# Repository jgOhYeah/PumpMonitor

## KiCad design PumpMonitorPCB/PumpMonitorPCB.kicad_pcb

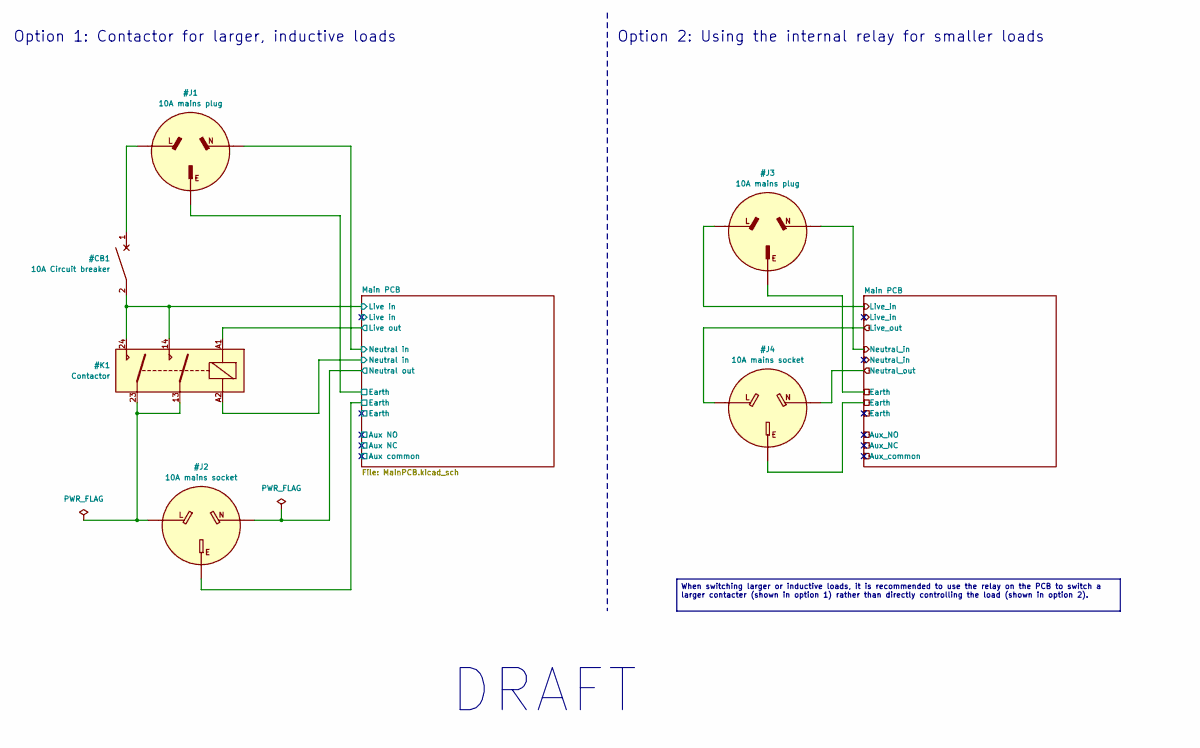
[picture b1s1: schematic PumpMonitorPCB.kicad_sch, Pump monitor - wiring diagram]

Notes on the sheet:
DRAFT
Option 2: Using the internal relay for smaller loads
Option 1: Contactor for larger, inductive loads
When switching larger or inductive loads, it is recommended to use the relay on the PCB to switch a larger contacter (shown in option 1) rather than directly controlling the load (shown in option 2).

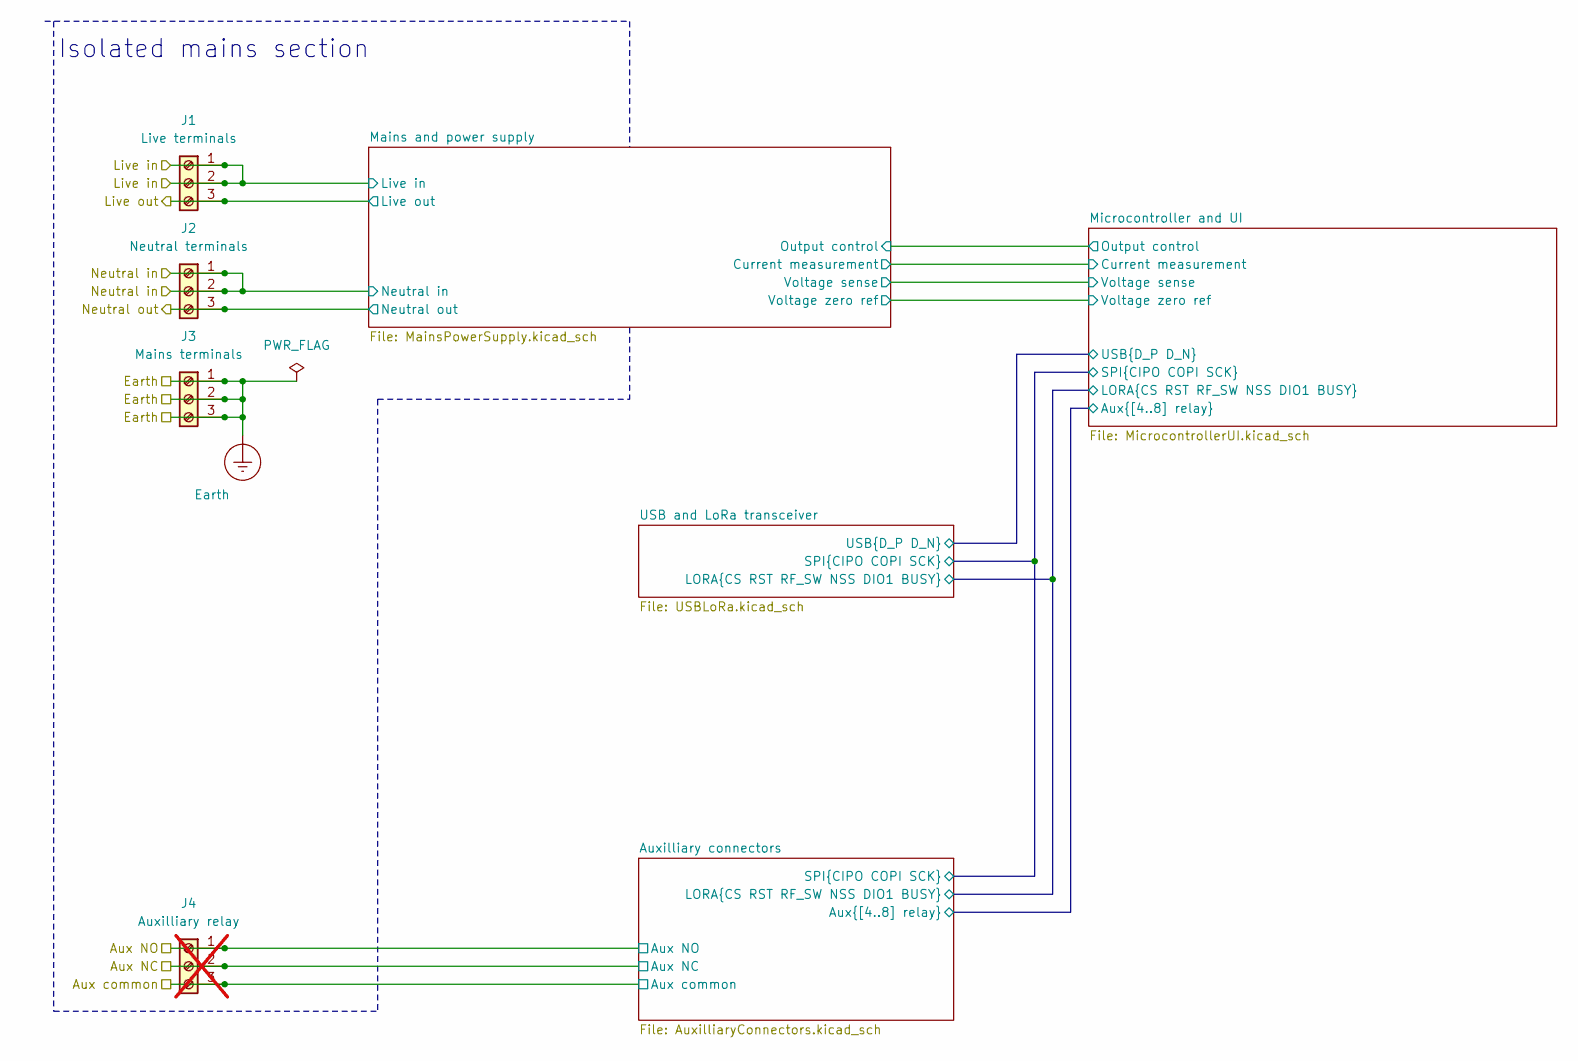
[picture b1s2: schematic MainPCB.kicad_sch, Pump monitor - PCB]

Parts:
J1: Live terminals; 8.25mm_ScrewTerminals
J2: Neutral terminals; 8.25mm_ScrewTerminals
J3: Mains terminals; 8.25mm_ScrewTerminals
J4: Auxilliary relay; 8.25mm_ScrewTerminals; not fitted

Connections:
/Main PCB/Aux NC: J4.2; also elsewhere on the board
/Main PCB/Aux NO: J4.1; also elsewhere on the board
/Main PCB/Aux common: J4.3; also elsewhere on the board
/Main PCB/Live in: J1.1, J1.2; also elsewhere on the board
/Main PCB/Live out: J1.3; also elsewhere on the board
/Main PCB/Neutral in: J2.1, J2.2; also elsewhere on the board
/Main PCB/Neutral out: J2.3; also elsewhere on the board
Earth: J3.1, J3.2, J3.3

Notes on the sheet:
Isolated mains section

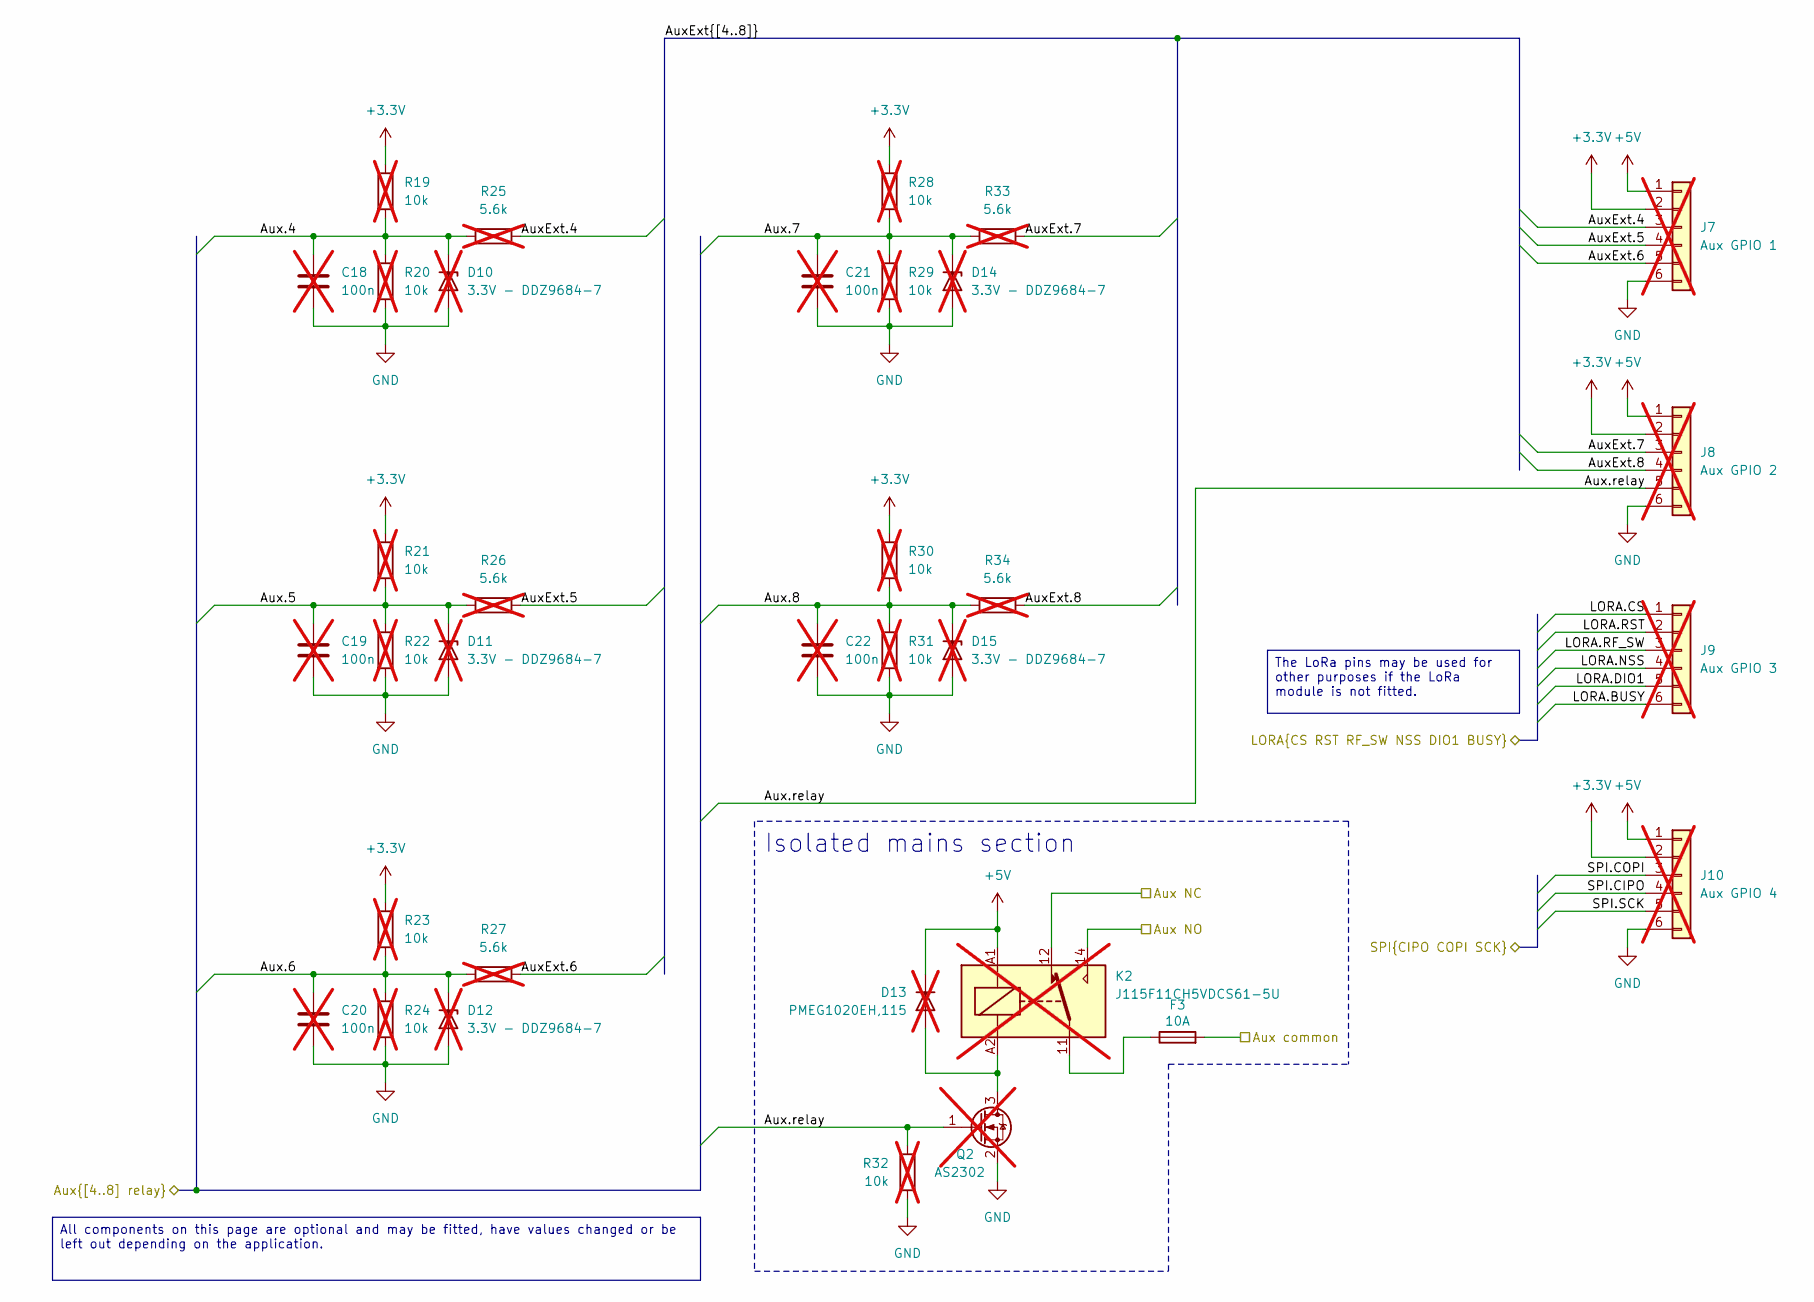
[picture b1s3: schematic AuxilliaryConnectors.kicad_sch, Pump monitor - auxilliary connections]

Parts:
C18, C19, C20, C21, C22: 100n; C_0603_1608Metric_Pad1.08x0.95mm_HandSolder; DigikeyNumber 311-1088-1-ND; not fitted
D10, D11, D12, D14, D15: 3.3V - DDZ9684-7; D_SOD-123F; DigikeyNumber DDZ9684-7DICT-ND; not fitted
D13: PMEG1020EH,115; D_SOD-123F; DigikeyNumber 1727-3849-1-ND; not fitted
F3: 10A; Fuseholder_Cylinder-5x20mm_Stelvio-Kontek_PTF78_Horizontal_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; Part number 696103201002; DigikeyNumber 732-11372-ND
J7: Aux GPIO 1; PinHeader_1x06_P2.54mm_Vertical; not fitted
J8: Aux GPIO 2; PinHeader_1x06_P2.54mm_Vertical; not fitted
J9: Aux GPIO 3; PinHeader_1x06_P2.54mm_Vertical; not fitted
J10: Aux GPIO 4; PinHeader_1x06_P2.54mm_Vertical; not fitted
K2: J115F11CH5VDCS61-5U; DigikeyNumber 2449-J115F11CH5VDCS61.5U-ND; not fitted
Q2: AS2302; TSOT-23; DigikeyNumber 4530-AS2302CT-ND; not fitted
R19, R20, R21, R22, R23, R24, R28, R29, R30, R31, R32: 10k; R_0603_1608Metric_Pad0.98x0.95mm_HandSolder; not fitted
R25, R26, R27, R33, R34: 5.6k; R_0603_1608Metric_Pad0.98x0.95mm_HandSolder; not fitted

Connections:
+3.3V: J7.2, J8.2, J10.2, R19.1, R21.1, R23.1, R28.1, R30.1; also elsewhere on the board
+5V: D13.1 (K), J7.1, J8.1, J10.1, K2.A1; also elsewhere on the board
/Main PCB/Aux NC: K2.12; also elsewhere on the board
/Main PCB/Aux NO: K2.14; also elsewhere on the board
/Main PCB/Aux common: F3.2; also elsewhere on the board
/Main PCB/Auxilliary connectors/Aux.4: C18.1, D10.1 (K), R19.2, R20.1, R25.1; also elsewhere on the board
/Main PCB/Auxilliary connectors/Aux.5: C19.1, D11.1 (K), R21.2, R22.1, R26.1; also elsewhere on the board
/Main PCB/Auxilliary connectors/Aux.6: C20.1, D12.1 (K), R23.2, R24.1, R27.1; also elsewhere on the board
/Main PCB/Auxilliary connectors/Aux.7: C21.1, D14.1 (K), R28.2, R29.1, R33.1; also elsewhere on the board
/Main PCB/Auxilliary connectors/Aux.8: C22.1, D15.1 (K), R30.2, R31.1, R34.1; also elsewhere on the board
/Main PCB/Auxilliary connectors/Aux.relay: J8.5, Q2.1 (G), R32.1; also elsewhere on the board
/Main PCB/Auxilliary connectors/AuxExt.4: J7.3, R25.2
/Main PCB/Auxilliary connectors/AuxExt.5: J7.4, R26.2
/Main PCB/Auxilliary connectors/AuxExt.6: J7.5, R27.2
/Main PCB/Auxilliary connectors/AuxExt.7: J8.3, R33.2
/Main PCB/Auxilliary connectors/AuxExt.8: J8.4, R34.2
/Main PCB/Auxilliary connectors/LORA.BUSY: J9.6; also elsewhere on the board
/Main PCB/Auxilliary connectors/LORA.CS: J9.1; also elsewhere on the board
/Main PCB/Auxilliary connectors/LORA.DIO1: J9.5; also elsewhere on the board
/Main PCB/Auxilliary connectors/LORA.NSS: J9.4; also elsewhere on the board
/Main PCB/Auxilliary connectors/LORA.RF_SW: J9.3; also elsewhere on the board
/Main PCB/Auxilliary connectors/LORA.RST: J9.2; also elsewhere on the board
/Main PCB/Auxilliary connectors/SPI.CIPO: J10.4; also elsewhere on the board
/Main PCB/Auxilliary connectors/SPI.COPI: J10.3; also elsewhere on the board
/Main PCB/Auxilliary connectors/SPI.SCK: J10.5; also elsewhere on the board
GND: C18.2, C19.2, C20.2, C21.2, C22.2, D10.2 (A), D11.2 (A), D12.2 (A), D14.2 (A), D15.2 (A), J7.6, J8.6, J10.6, Q2.2 (S), R20.2, R22.2, R24.2, R29.2, R31.2, R32.2; also elsewhere on the board
unnamed: D13.2 (A), K2.A2, Q2.3 (D)
unnamed: F3.1, K2.11

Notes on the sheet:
Isolated mains section
All components on this page are optional and may be fitted, have values changed or be left out depending on the application.
The LoRa pins may be used for other purposes if the LoRa module is not fitted.

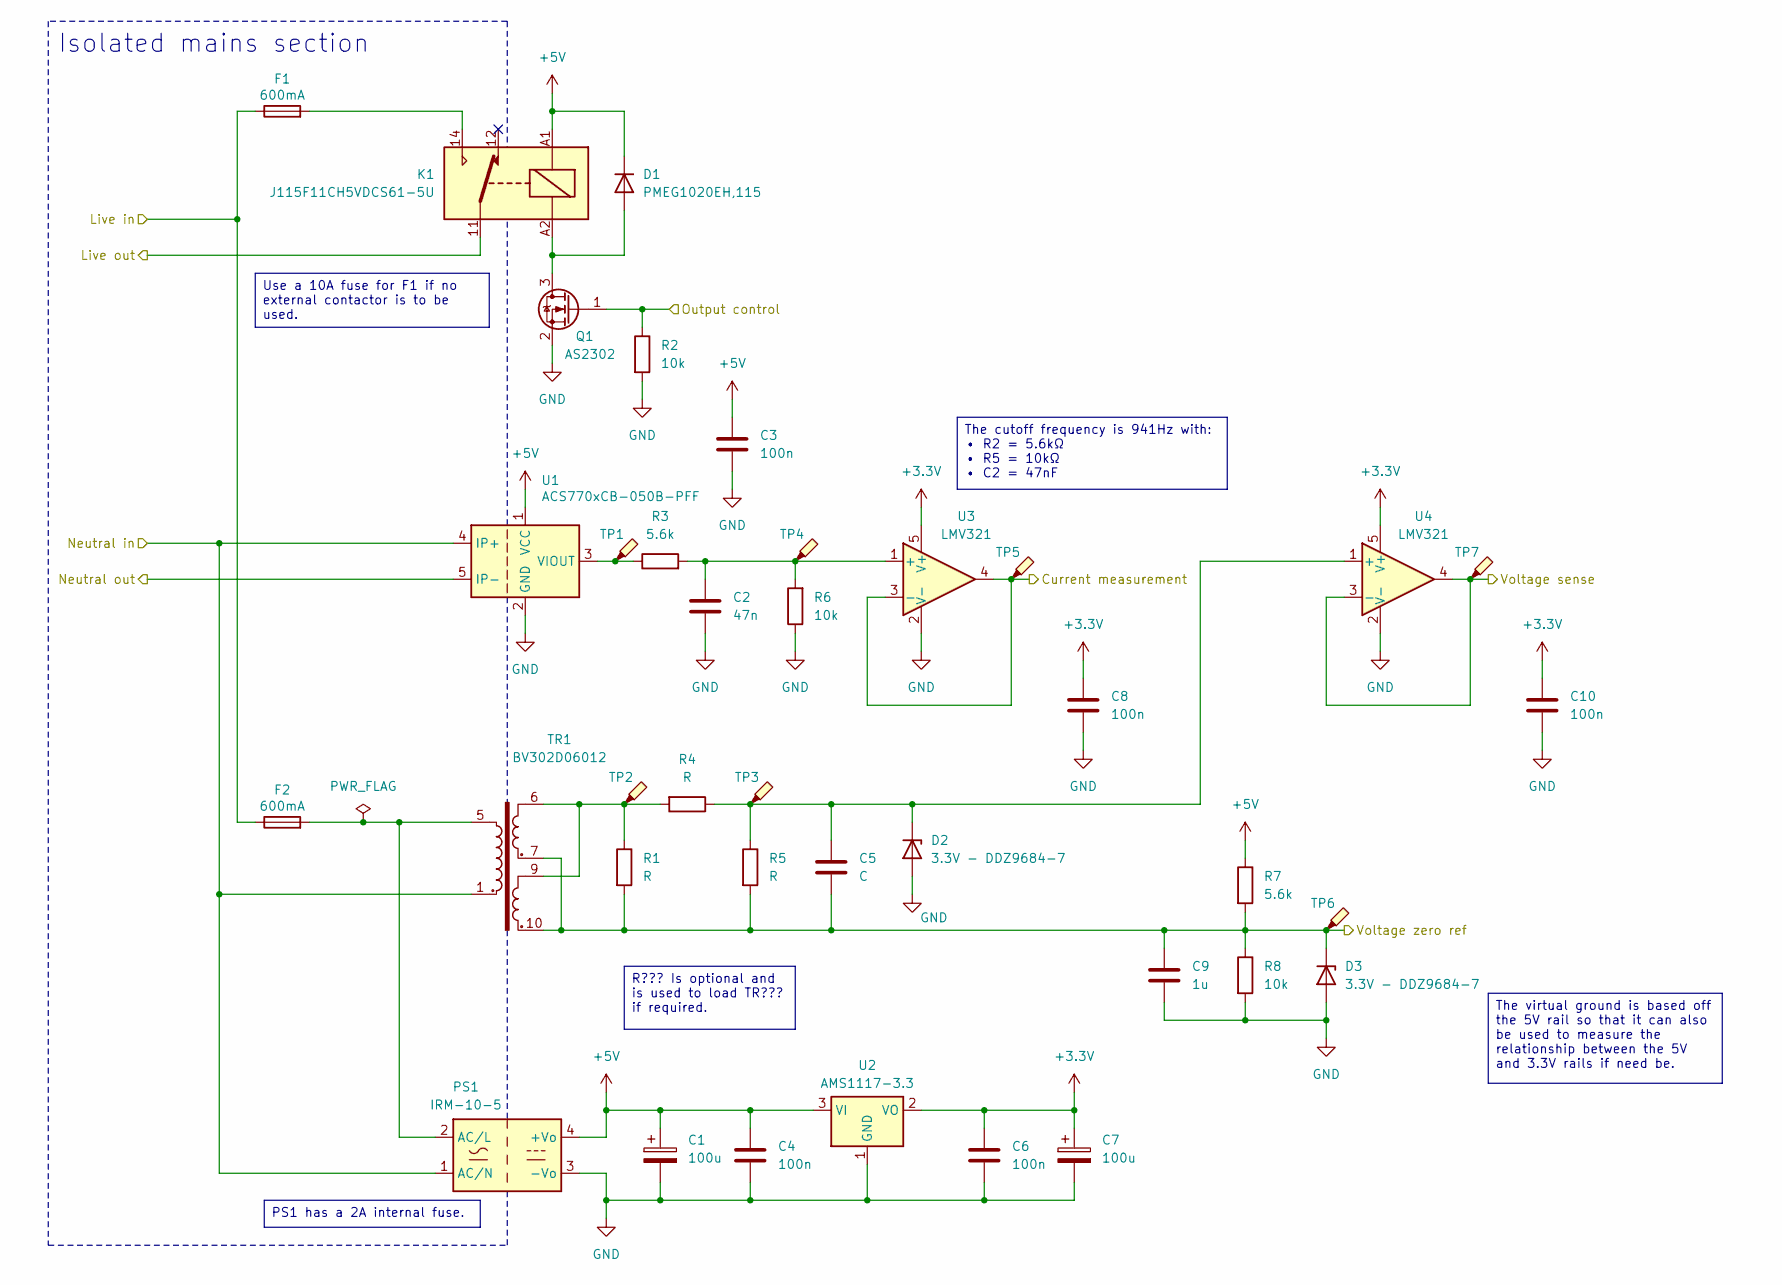
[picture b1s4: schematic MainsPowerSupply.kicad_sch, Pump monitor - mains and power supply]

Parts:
C1, C7: 100u; CP_Radial_D10.0mm_P3.80mm
C2: 47n; C_0603_1608Metric_Pad1.08x0.95mm_HandSolder; DigikeyNumber 1276-2079-1-ND
C3, C4, C6, C8, C10: 100n; C_0603_1608Metric_Pad1.08x0.95mm_HandSolder; DigikeyNumber 311-1088-1-ND
C5: C; C_0603_1608Metric_Pad1.08x0.95mm_HandSolder
C9: 1u; C_0603_1608Metric_Pad1.08x0.95mm_HandSolder; DigikeyNumber 587-1241-1-ND
D1: PMEG1020EH,115; D_SOD-123F; DigikeyNumber 1727-3849-1-ND
D2, D3: 3.3V - DDZ9684-7; D_SOD-123F; DigikeyNumber DDZ9684-7DICT-ND
F1, F2: 600mA; Fuseholder_Cylinder-5x20mm_Stelvio-Kontek_PTF78_Horizontal_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; Part number 696103201002; DigikeyNumber 732-11372-ND
K1: J115F11CH5VDCS61-5U; DigikeyNumber 2449-J115F11CH5VDCS61.5U-ND
PS1: IRM-10-5; Converter_ACDC_MeanWell_IRM-10-xx_THT; DigikeyNumber 1866-3032-ND
Q1: AS2302; TSOT-23; DigikeyNumber 4530-AS2302CT-ND
R1: R; R_Axial_DIN0309_L9.0mm_D3.2mm_P12.70mm_Horizontal
R2, R6, R8: 10k; R_0603_1608Metric_Pad0.98x0.95mm_HandSolder
R3, R7: 5.6k; R_0603_1608Metric_Pad0.98x0.95mm_HandSolder
R4, R5: R; R_0603_1608Metric_Pad0.98x0.95mm_HandSolder
TP1, TP2, TP3, TP4, TP5, TP6, TP7: TestPoint_THTPad_D1.5mm_Drill0.7mm
TR1: BV302D06012; Transformer_BV302D06012
U1: ACS770xCB-050B-PFF; Allegro_CB_PFF
U2: AMS1117-3.3; SOT-223-3_TabPin2
U3, U4: LMV321; SOT-23-5_HandSoldering

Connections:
+3.3V: C6.1, C7.1, C8.1, C10.1, U2.2 (VO), U3.5 (V+), U4.5 (V+); also elsewhere on the board
+5V: C1.1, C3.1, C4.1, D1.1 (K), K1.A1, PS1.4 (+Vo), R7.1, U1.1 (VCC), U2.3 (VI); also elsewhere on the board
/Main PCB/Live in: F1.1, F2.1; also elsewhere on the board
/Main PCB/Live out: K1.11; also elsewhere on the board
/Main PCB/Mains and power supply/Current measurement: TP5.1, U3.3 (-), U3.4; also elsewhere on the board
/Main PCB/Mains and power supply/Output control: Q1.1 (G), R2.1; also elsewhere on the board
/Main PCB/Mains and power supply/Voltage sense: TP7.1, U4.3 (-), U4.4; also elsewhere on the board
/Main PCB/Mains and power supply/Voltage zero ref: C5.2, C9.1, D3.1 (K), R1.2, R5.2, R7.2, R8.1, TP6.1, TR1.7, TR1.10; also elsewhere on the board
/Main PCB/Neutral in: PS1.1 (AC/N), TR1.1, U1.4 (IP+); also elsewhere on the board
/Main PCB/Neutral out: U1.5 (IP-); also elsewhere on the board
GND: C1.2, C2.2, C3.2, C4.2, C6.2, C7.2, C8.2, C9.2, C10.2, D2.2 (A), D3.2 (A), PS1.3 (-Vo), Q1.2 (S), R2.2, R6.1, R8.2, U1.2 (GND), U2.1 (GND), U3.2 (V-), U4.2 (V-); also elsewhere on the board
unnamed: D1.2 (A), K1.A2, Q1.3 (D)
unnamed: C5.1, D2.1 (K), R4.1, R5.1, TP3.1, U4.1 (+)
unnamed: F1.2, K1.14
unnamed: F2.2, PS1.2 (AC/L), TR1.5
unnamed: R1.1, R4.2, TP2.1, TR1.6, TR1.9
unnamed: R3.1, TP1.1, U1.3 (VIOUT)
unnamed: C2.1, R3.2, R6.2, TP4.1, U3.1 (+)

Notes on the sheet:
Isolated mains section
The virtual ground is based off the 5V rail so that it can also be used to measure the relationship between the 5V and 3.3V rails if need be.
R??? Is optional and is used to load TR??? if required.
The cutoff frequency is 941Hz with: • R2 = 5.6kΩ • R5 = 10kΩ • C2 = 47nF
PS1 has a 2A internal fuse.
Use a 10A fuse for F1 if no external contactor is to be used.

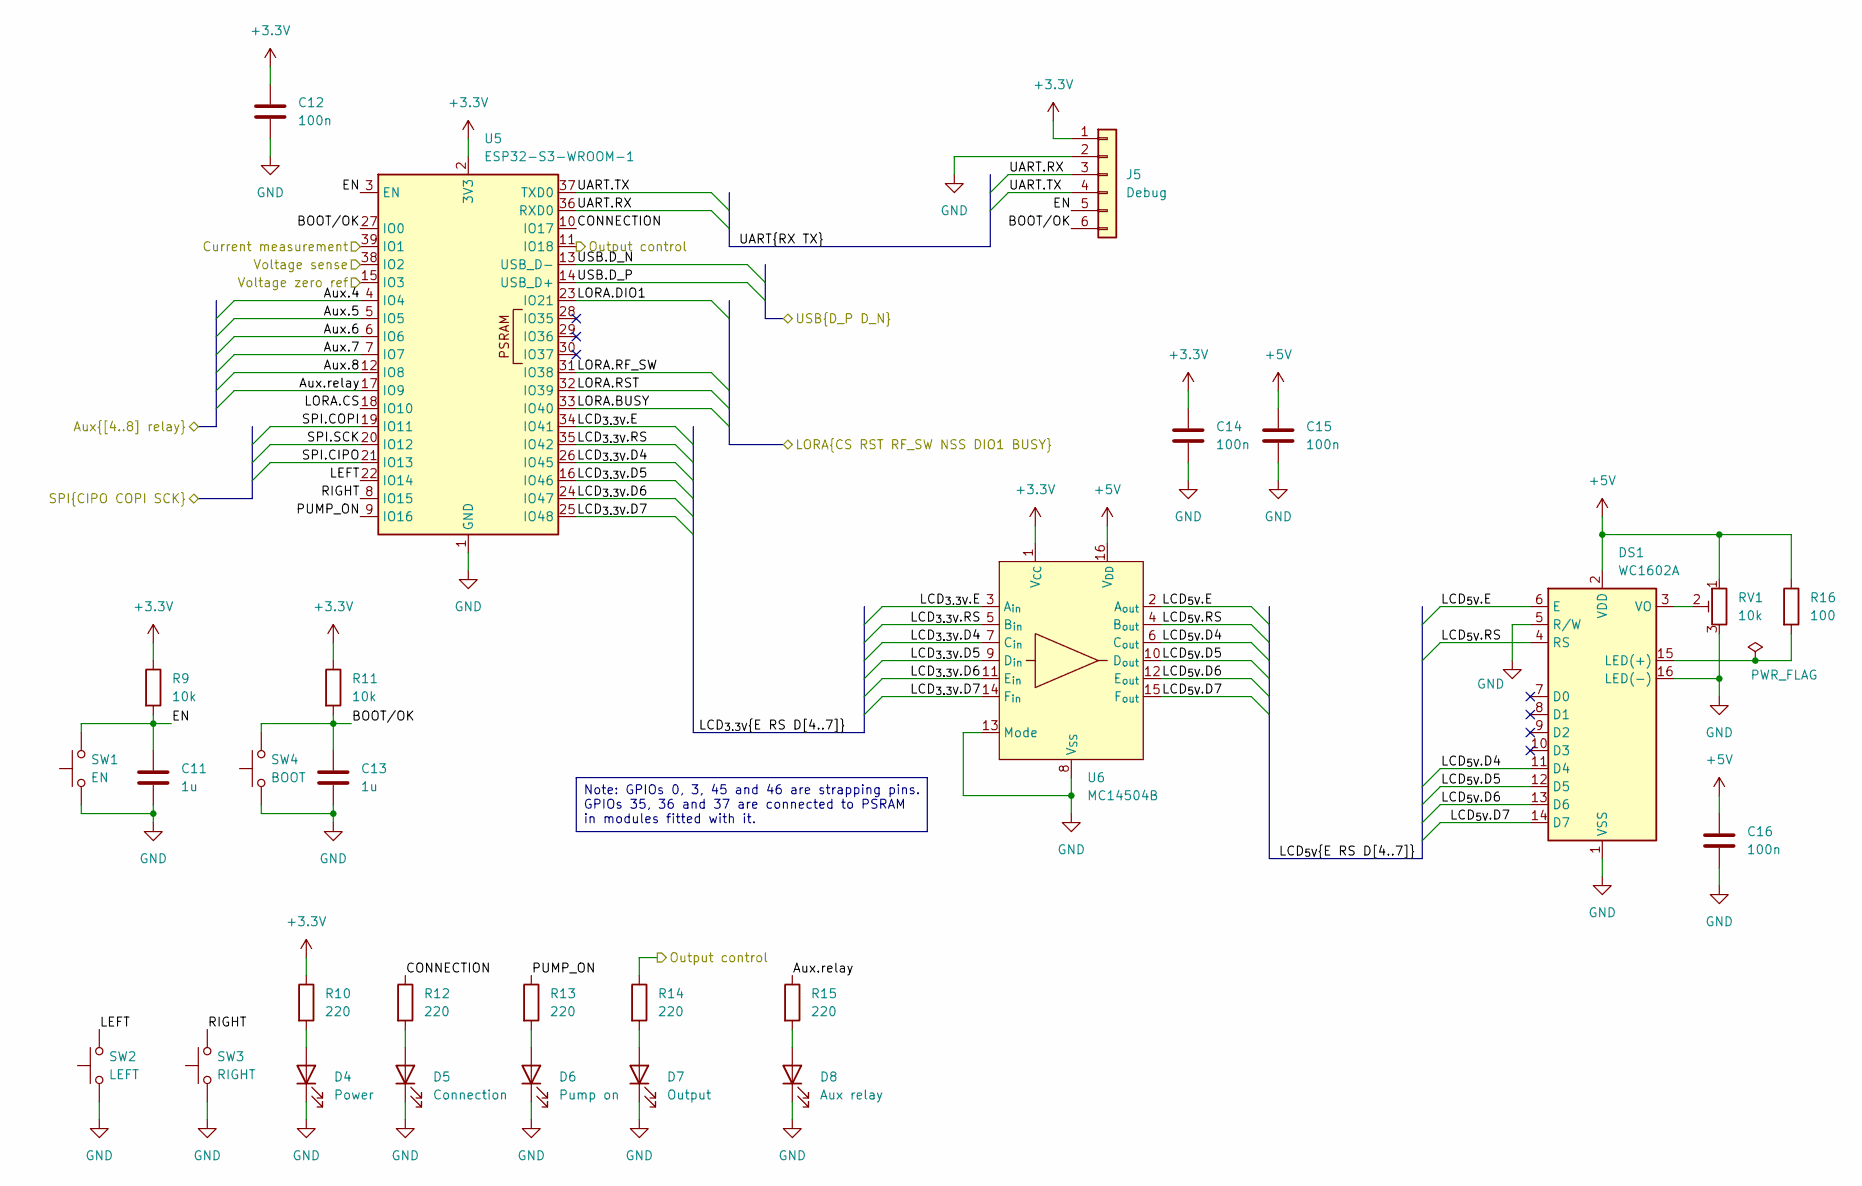
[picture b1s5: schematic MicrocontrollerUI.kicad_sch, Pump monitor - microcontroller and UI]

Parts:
C11, C13: 1u; C_0603_1608Metric_Pad1.08x0.95mm_HandSolder; DigikeyNumber 587-1241-1-ND
C12, C14, C15, C16: 100n; C_0603_1608Metric_Pad1.08x0.95mm_HandSolder; DigikeyNumber 311-1088-1-ND
D4: Power; LED_D5.0mm
D5: Connection; LED_D5.0mm
D6: Pump on; LED_D5.0mm
D7: Output; LED_D5.0mm
D8: Aux relay; LED_D5.0mm
DS1: WC1602A; PinHeader_2x08_P2.54mm_Vertical
J5: Debug; PinHeader_1x06_P2.54mm_Vertical
R9, R11: 10k; R_0603_1608Metric_Pad0.98x0.95mm_HandSolder
R10, R12, R13, R14, R15: 220; R_0603_1608Metric_Pad0.98x0.95mm_HandSolder
R16: 100; R_Axial_DIN0309_L9.0mm_D3.2mm_P12.70mm_Horizontal
RV1: 10k; Potentiometer_ACP_CA9-V10_Vertical
SW1: EN; SW_Tactile_SPST_Angled_PTS645Vx39-2LFS
SW2: LEFT; PinHeader_1x02_P2.54mm_Vertical
SW3: RIGHT; PinHeader_1x02_P2.54mm_Vertical
SW4: BOOT; PinHeader_1x02_P2.54mm_Vertical
U5: ESP32-S3-WROOM-1
U6: MC14504B; TSSOP-16_4.4x5mm_P0.65mm

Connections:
+3.3V: C12.1, C14.1, J5.1, R9.1, R10.1, R11.1, U5.2 (3V3), U6.1 (V_{CC}); also elsewhere on the board
+5V: C15.1, C16.1, DS1.2 (VDD), R16.1, RV1.1, U6.16 (V_{DD}); also elsewhere on the board
/Main PCB/Auxilliary connectors/Aux.4: U5.4 (IO4); also elsewhere on the board
/Main PCB/Auxilliary connectors/Aux.5: U5.5 (IO5); also elsewhere on the board
/Main PCB/Auxilliary connectors/Aux.6: U5.6 (IO6); also elsewhere on the board
/Main PCB/Auxilliary connectors/Aux.7: U5.7 (IO7); also elsewhere on the board
/Main PCB/Auxilliary connectors/Aux.8: U5.12 (IO8); also elsewhere on the board
/Main PCB/Auxilliary connectors/Aux.relay: R15.1, U5.17 (IO9); also elsewhere on the board
/Main PCB/Auxilliary connectors/LORA.BUSY: U5.33 (IO40); also elsewhere on the board
/Main PCB/Auxilliary connectors/LORA.CS: U5.18 (IO10); also elsewhere on the board
/Main PCB/Auxilliary connectors/LORA.DIO1: U5.23 (IO21); also elsewhere on the board
/Main PCB/Auxilliary connectors/LORA.RF_SW: U5.31 (IO38); also elsewhere on the board
/Main PCB/Auxilliary connectors/LORA.RST: U5.32 (IO39); also elsewhere on the board
/Main PCB/Auxilliary connectors/SPI.CIPO: U5.21 (IO13); also elsewhere on the board
/Main PCB/Auxilliary connectors/SPI.COPI: U5.19 (IO11); also elsewhere on the board
/Main PCB/Auxilliary connectors/SPI.SCK: U5.20 (IO12); also elsewhere on the board
/Main PCB/Mains and power supply/Current measurement: U5.39 (IO1); also elsewhere on the board
/Main PCB/Mains and power supply/Output control: R14.1, U5.11 (IO18); also elsewhere on the board
/Main PCB/Mains and power supply/Voltage sense: U5.38 (IO2); also elsewhere on the board
/Main PCB/Mains and power supply/Voltage zero ref: U5.15 (IO3); also elsewhere on the board
/Main PCB/Microcontroller and UI/BOOT/OK: C13.2, J5.6, R11.2, SW4.2, U5.27 (IO0)
/Main PCB/Microcontroller and UI/CONNECTION: R12.1, U5.10 (IO17)
/Main PCB/Microcontroller and UI/EN: C11.2, J5.5, R9.2, SW1.2, U5.3 (EN)
/Main PCB/Microcontroller and UI/LCD_{3.3V}.D4: U5.26 (IO45), U6.7 (C_{in})
/Main PCB/Microcontroller and UI/LCD_{3.3V}.D5: U5.16 (IO46), U6.9 (D_{in})
/Main PCB/Microcontroller and UI/LCD_{3.3V}.D6: U5.24 (IO47), U6.11 (E_{in})
/Main PCB/Microcontroller and UI/LCD_{3.3V}.D7: U5.25 (IO48), U6.14 (F_{in})
/Main PCB/Microcontroller and UI/LCD_{3.3V}.E: U5.34 (IO41), U6.3 (A_{in})
/Main PCB/Microcontroller and UI/LCD_{3.3V}.RS: U5.35 (IO42), U6.5 (B_{in})
/Main PCB/Microcontroller and UI/LCD_{5V}.D4: DS1.11 (D4), U6.6 (C_{out})
/Main PCB/Microcontroller and UI/LCD_{5V}.D5: DS1.12 (D5), U6.10 (D_{out})
/Main PCB/Microcontroller and UI/LCD_{5V}.D6: DS1.13 (D6), U6.12 (E_{out})
/Main PCB/Microcontroller and UI/LCD_{5V}.D7: DS1.14 (D7), U6.15 (F_{out})
/Main PCB/Microcontroller and UI/LCD_{5V}.E: DS1.6 (E), U6.2 (A_{out})
/Main PCB/Microcontroller and UI/LCD_{5V}.RS: DS1.4 (RS), U6.4 (B_{out})
/Main PCB/Microcontroller and UI/LEFT: SW2.2, U5.22 (IO14)
/Main PCB/Microcontroller and UI/PUMP_ON: R13.1, U5.9 (IO16)
/Main PCB/Microcontroller and UI/RIGHT: SW3.2, U5.8 (IO15)
/Main PCB/Microcontroller and UI/UART.RX: J5.3, U5.36 (RXD0)
/Main PCB/Microcontroller and UI/UART.TX: J5.4, U5.37 (TXD0)
/Main PCB/Microcontroller and UI/USB.D_N: U5.13 (USB_D-); also elsewhere on the board
/Main PCB/Microcontroller and UI/USB.D_P: U5.14 (USB_D+); also elsewhere on the board
GND: C11.1, C12.2, C13.1, C14.2, C15.2, C16.2, D4.1 (K), D5.1 (K), D6.1 (K), D7.1 (K), D8.1 (K), DS1.1 (VSS), DS1.5 (R/W), DS1.16 (LED(-)), J5.2, RV1.3, SW1.1, SW2.1, SW3.1, SW4.1, U5.1 (GND), U5.40 (GND), U5.41 (GND), U6.8 (V_{SS}), U6.13 (Mode); also elsewhere on the board
unnamed: D4.2 (A), R10.2
unnamed: D5.2 (A), R12.2
unnamed: D6.2 (A), R13.2
unnamed: D7.2 (A), R14.2
unnamed: D8.2 (A), R15.2
unnamed: DS1.15 (LED(+)), R16.2
unnamed: DS1.3 (VO), RV1.2

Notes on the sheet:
Note: GPIOs 0, 3, 45 and 46 are strapping pins. GPIOs 35, 36 and 37 are connected to PSRAM in modules fitted with it.

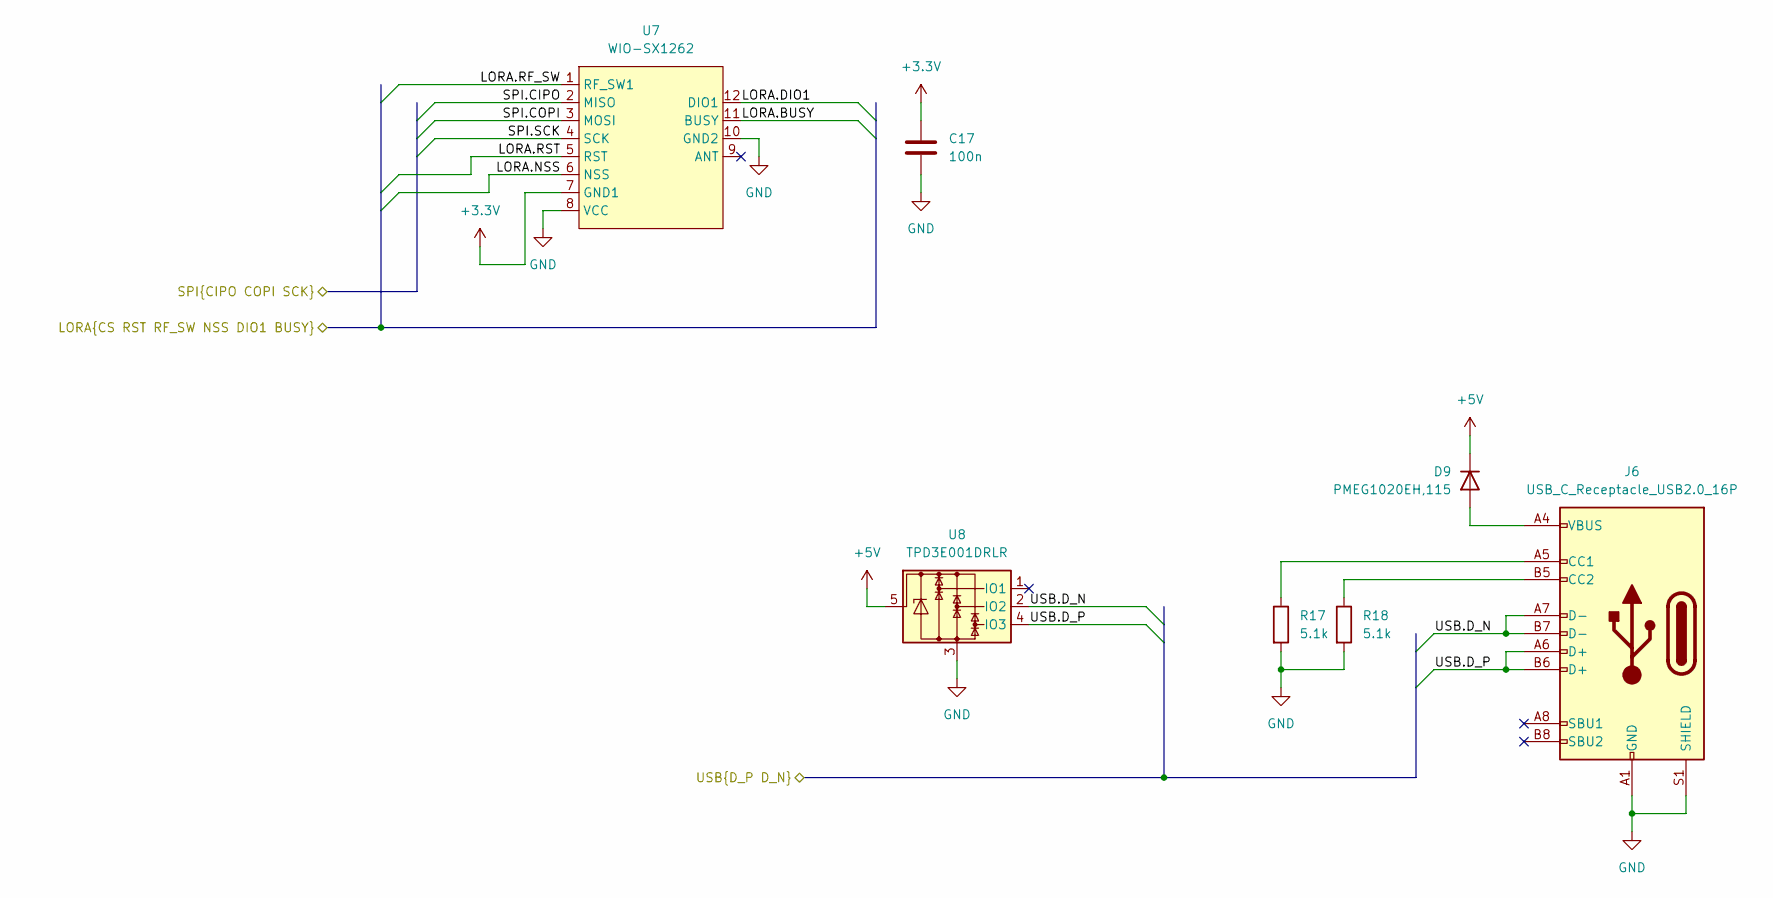
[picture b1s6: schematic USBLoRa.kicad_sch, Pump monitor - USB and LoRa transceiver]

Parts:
C17: 100n; C_0603_1608Metric_Pad1.08x0.95mm_HandSolder; DigikeyNumber 311-1088-1-ND
D9: PMEG1020EH,115; D_SOD-123F; DigikeyNumber 1727-3849-1-ND
J6: USB_C_Receptacle_USB2.0_16P; USB_C_Receptacle_GCT_USB4105-xx-A_16P_TopMnt_Horizontal
R17, R18: 5.1k; R_0603_1608Metric_Pad0.98x0.95mm_HandSolder
U7: WIO-SX1262; Wio-SX1262 PCB Package
U8: TPD3E001DRLR; SOT-553

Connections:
+3.3V: C17.1, U7.7 (GND1); also elsewhere on the board
+5V: D9.1 (K), U8.5; also elsewhere on the board
/Main PCB/Auxilliary connectors/LORA.BUSY: U7.11 (BUSY); also elsewhere on the board
/Main PCB/Auxilliary connectors/LORA.DIO1: U7.12 (DIO1); also elsewhere on the board
/Main PCB/Auxilliary connectors/LORA.NSS: U7.6 (NSS); also elsewhere on the board
/Main PCB/Auxilliary connectors/LORA.RF_SW: U7.1 (RF_SW1); also elsewhere on the board
/Main PCB/Auxilliary connectors/LORA.RST: U7.5 (RST); also elsewhere on the board
/Main PCB/Auxilliary connectors/SPI.CIPO: U7.2 (MISO); also elsewhere on the board
/Main PCB/Auxilliary connectors/SPI.COPI: U7.3 (MOSI); also elsewhere on the board
/Main PCB/Auxilliary connectors/SPI.SCK: U7.4 (SCK); also elsewhere on the board
/Main PCB/Microcontroller and UI/USB.D_N: J6.A7 (D-), J6.B7 (D-), U8.2 (IO2); also elsewhere on the board
/Main PCB/Microcontroller and UI/USB.D_P: J6.A6 (D+), J6.B6 (D+), U8.4 (IO3); also elsewhere on the board
GND: C17.2, J6.A1 (GND), J6.A12 (GND), J6.B1 (GND), J6.B12 (GND), J6.S1 (SHIELD), R17.2, R18.2, U7.8 (VCC), U7.10 (GND2), U8.3; also elsewhere on the board
unnamed: D9.2 (A), J6.A4 (VBUS), J6.A9 (VBUS), J6.B4 (VBUS), J6.B9 (VBUS)
unnamed: J6.A5 (CC1), R17.1
unnamed: J6.B5 (CC2), R18.1

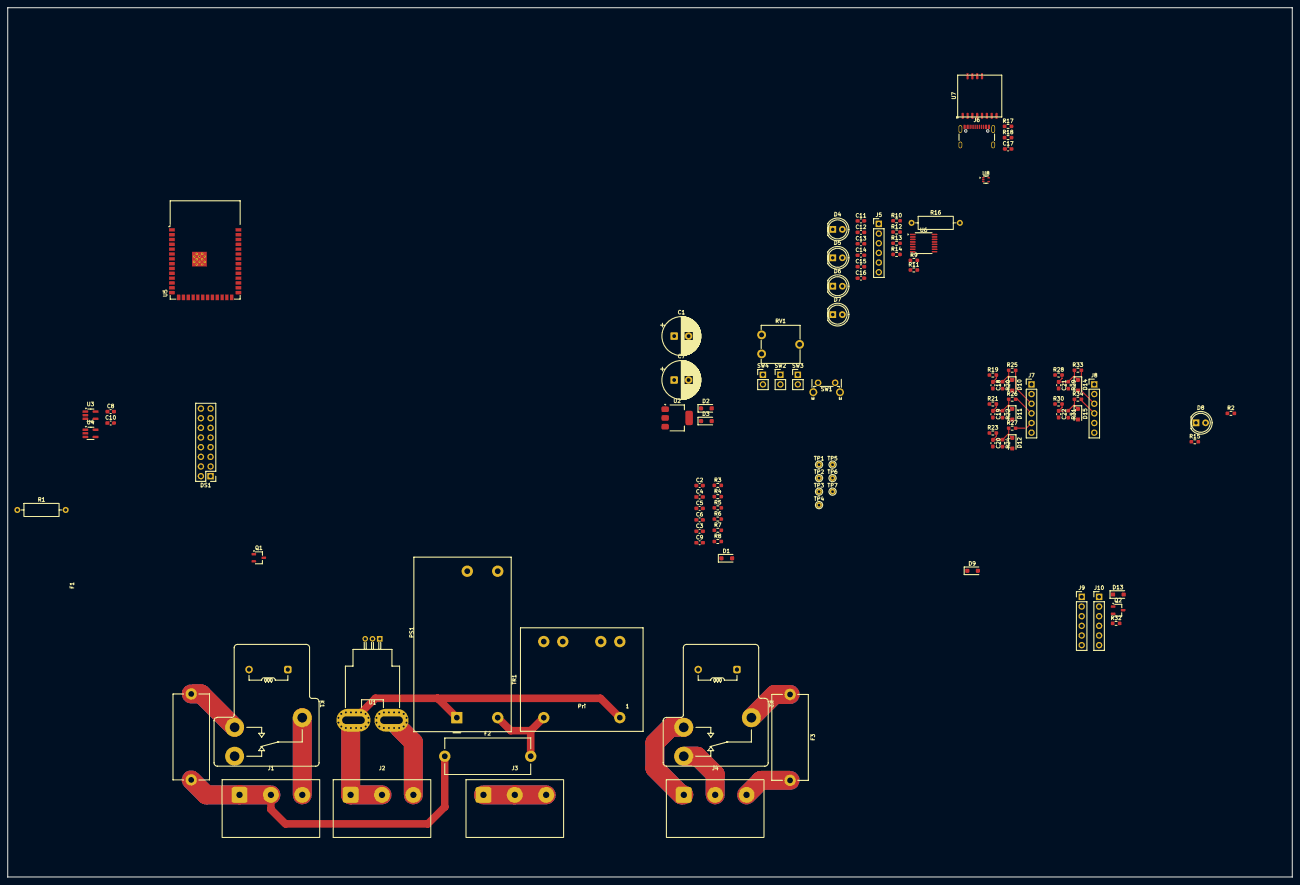
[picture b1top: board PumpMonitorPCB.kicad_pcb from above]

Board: 2 copper layers, 337.8 x 228.6 mm, 111 parts (0 on the bottom side), 76 nets.

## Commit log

2025-09-11 Rearranging to include a wiring diagram and contactor.
2025-09-22 Adding microcontroller, USB, UI components.
2025-09-25 Tidied schematic, added LoRa module.
2025-09-26 Added aux. connectors, started assigning components.
2025-09-27 Added op amps to voltage and current measurement, more footprint assignments.
2025-09-27 Swapped current measurement to neutral (wiring diagram needs updating).
2025-09-29 Made smaller mains connector symbols, added multiple options to wiring diagram,
2025-10-01 Added terminals footprint and 3D model.
2025-10-07 Rejigged auxilliary connectors, experimetning with kiclearance.
2025-10-10 Added fuse on aux relay, setting creepage and clearance distances.
2025-10-18 Adding test points, CAD files
